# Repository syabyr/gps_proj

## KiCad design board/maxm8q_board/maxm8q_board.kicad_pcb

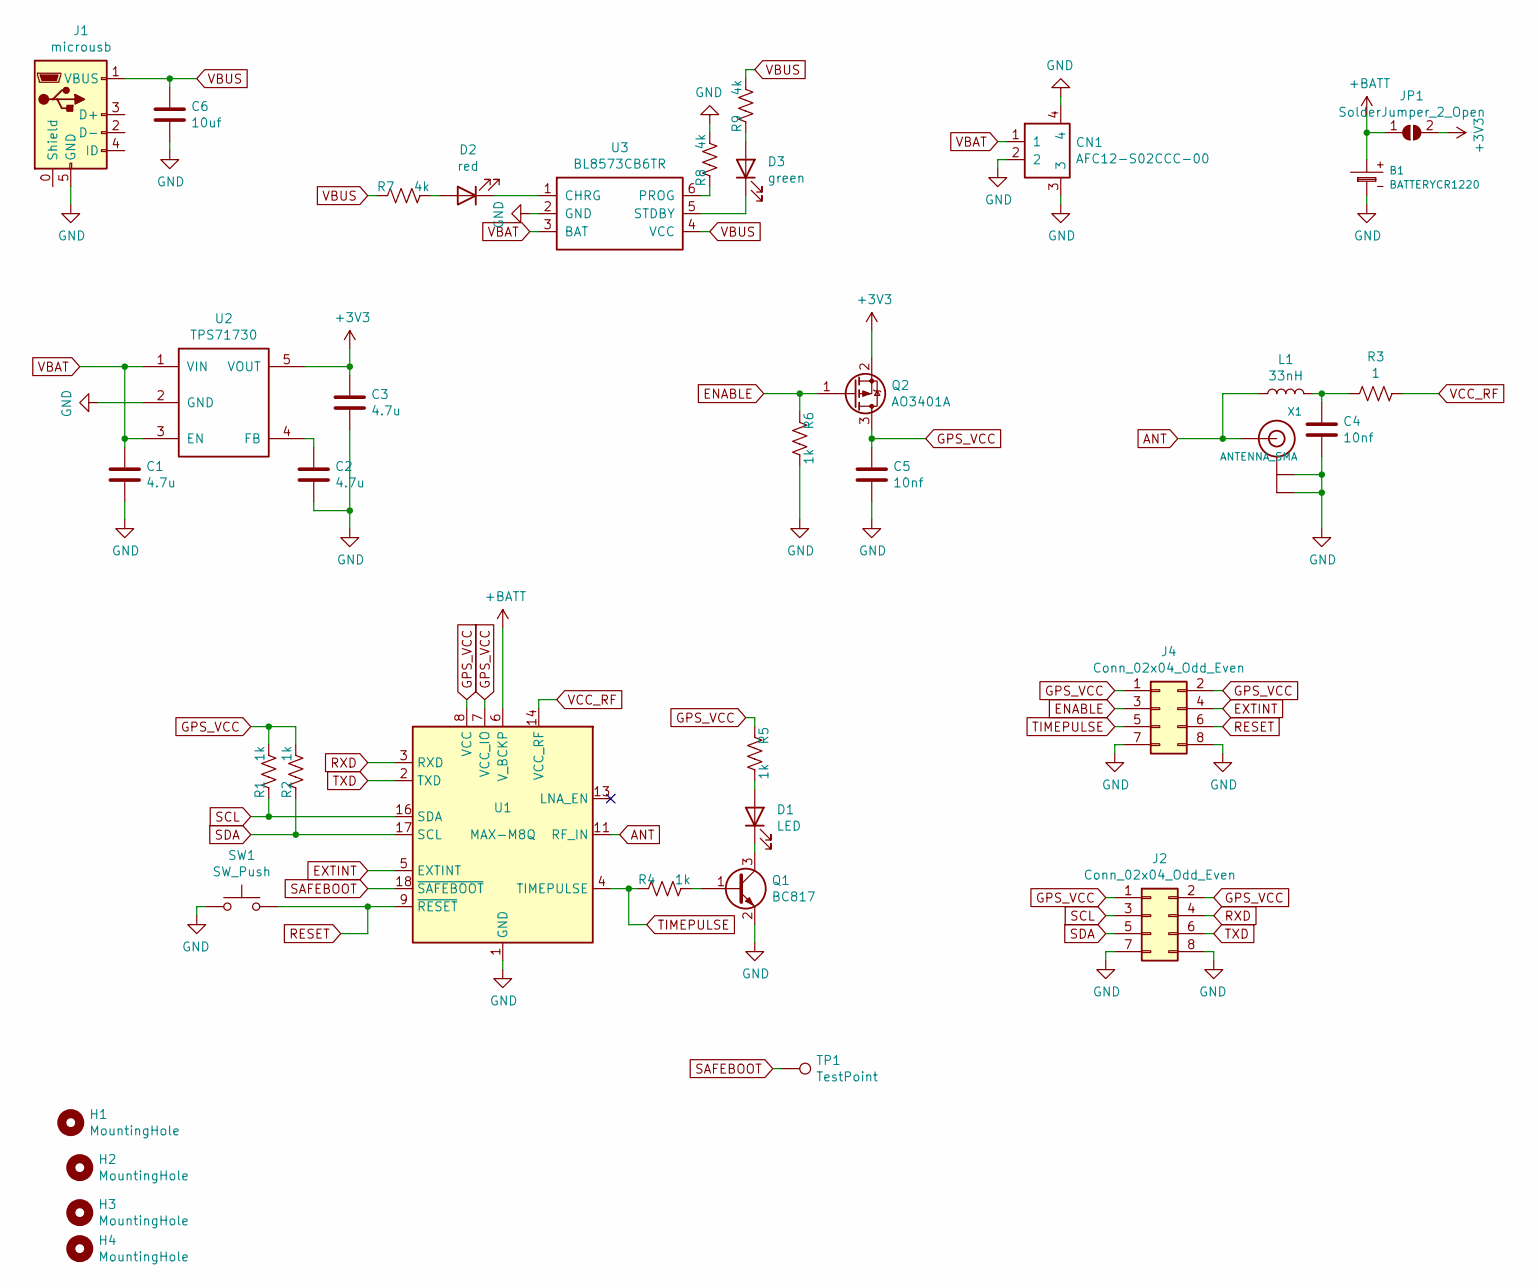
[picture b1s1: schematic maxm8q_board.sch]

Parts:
B1: BATTERYCR1220; CR1220-2
C1, C2, C3: 4.7u; C_0603_1608Metric_Pad1.08x0.95mm_HandSolder
C4, C5: 10nf; C_0402_1005Metric_Pad0.74x0.62mm_HandSolder
C6: 10uf; C_0805_2012Metric_Pad1.18x1.45mm_HandSolder
CN1: AFC12-S02CCC-00; CONN-SMD_AFC12-S02CCC-00
D1: LED; LED_0603_1608Metric_Pad1.05x0.95mm_HandSolder
D2: red; LED_0603_1608Metric_Pad1.05x0.95mm_HandSolder
D3: green; LED_0603_1608Metric_Pad1.05x0.95mm_HandSolder
H1, H2, H3, H4: MountingHole; MountingHole_3.2mm_M3_ISO7380
J1: microusb; USB_Micro-B_Wuerth_629105150521_CircularHoles
J2, J4: Conn_02x04_Odd_Even; PinHeader_2x04_P2.54mm_Vertical
JP1: SolderJumper_2_Open; SolderJumper-2_P1.3mm_Open_Pad1.0x1.5mm
L1: 33nH; L_0805_2012Metric_Pad1.15x1.40mm_HandSolder
Q1: BC817; SOT-23
Q2: AO3401A; SOT-23
R1, R2, R4, R5, R6: 1k; R_0402_1005Metric_Pad0.72x0.64mm_HandSolder
R3: 1; R_0603_1608Metric_Pad0.98x0.95mm_HandSolder
R7, R8, R9: 4k; R_0402_1005Metric_Pad0.72x0.64mm_HandSolder
SW1: SW_Push; turtlekey
TP1: TestPoint; TestPoint_THTPad_1.0x1.0mm_Drill0.5mm
U1: MAX-M8Q; ublox_MAX
U2: TPS71730; SOT-353_SC-70-5_Handsoldering
U3: BL8573CB6TR; SOT-23-6_Handsoldering
X1: ANTENNA_SMA; SMA_Samtec_SMA-J-P-X-ST-EM1_EdgeMount

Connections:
+3V3: C3.2, JP1.2 (B), Q2.2 (S), U2.5 (VOUT)
+BATT: B1.+, JP1.1 (A), U1.6 (V_BCKP)
ANT: L1.1, U1.11 (RF_IN), X1.1 (SIGNAL)
ENABLE: J4.3, Q2.1 (G), R6.1
EXTINT: J4.4, U1.5 (EXTINT)
GND: B1.-, C1.2, C2.1, C3.1, C4.2, C5.2, C6.2, CN1.2, CN1.3, CN1.4, J1.5 (GND), J2.7, J2.8, J4.7, J4.8, Q1.2 (E), R6.2, R8.2, SW1.2, U1.1 (GND), U1.10 (GND), U1.12 (GND), U2.2 (GND), U3.2 (GND), X1.2 (GND@0)
GPS_VCC: C5.1, J2.1, J2.2, J4.1, J4.2, Q2.3 (D), R1.2, R2.2, R5.1, U1.7 (VCC_IO), U1.8 (VCC)
unnamed: C2.2, U2.4 (FB)
unnamed: C4.1, L1.2, R3.2
unnamed: D1.1 (K), Q1.3 (C)
unnamed: D1.2 (A), R5.2
unnamed: D2.1 (K), U3.1 (CHRG)
unnamed: D2.2 (A), R7.2
unnamed: D3.1 (K), U3.5 (STDBY)
unnamed: D3.2 (A), R9.1
unnamed: Q1.1 (B), R4.2
unnamed: R8.1, U3.6 (PROG)
RESET: J4.6, SW1.1, U1.9 (~RESET)
RXD: J2.4, U1.3 (RXD)
SAFEBOOT: TP1.1, U1.18 (~SAFEBOOT)
SCL: J2.3, R1.1, U1.16 (SDA)
SDA: J2.5, R2.1, U1.17 (SCL)
TIMEPULSE: J4.5, R4.1, U1.4 (TIMEPULSE)
TXD: J2.6, U1.2 (TXD)
VBAT: C1.1, CN1.1, U2.1 (VIN), U2.3 (EN), U3.3 (BAT)
VBUS: C6.1, J1.1 (VBUS), R7.1, R9.2, U3.4 (VCC)
VCC_RF: R3.1, U1.14 (VCC_RF)

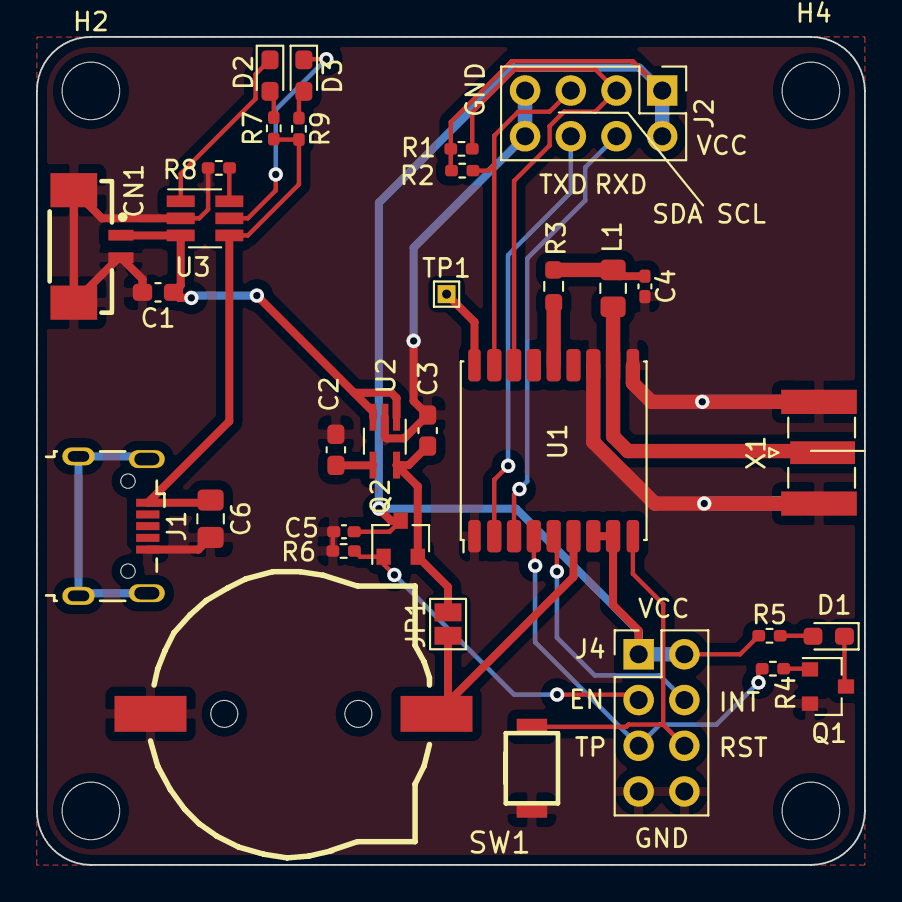
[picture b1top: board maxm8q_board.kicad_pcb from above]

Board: 2 copper layers, 46.0 x 46.0 mm, 37 parts (0 on the bottom side), 27 nets.

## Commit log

2021-07-25 max-m8q
